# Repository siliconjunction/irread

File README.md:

# Analyse and Send IR Remote Codes

## Overview

The program is used to analyse IR remote control codes and extract the parameters for the coding scheme. It can also send IR codes for testing. The hardware required is based on the ESP8266. The software is written in C on Mongoose OS.

<br/>
<center></center>
<br/>

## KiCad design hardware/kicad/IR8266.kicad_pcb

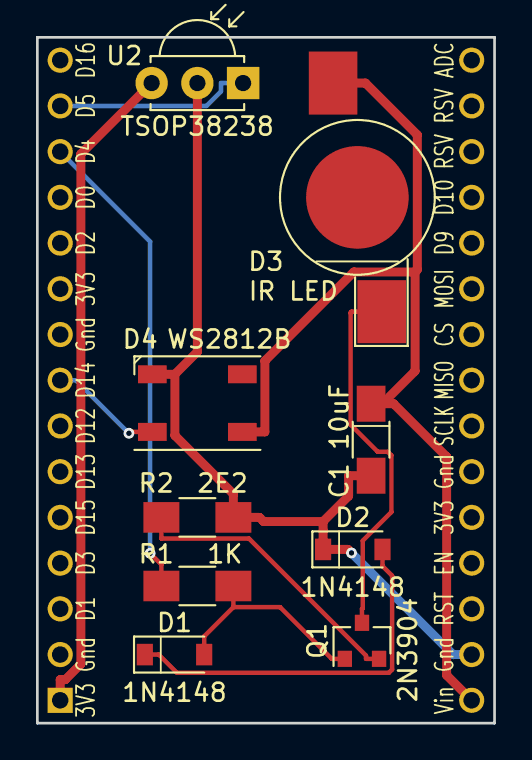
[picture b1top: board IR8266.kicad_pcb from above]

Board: 2 copper layers, 25.4 x 38.1 mm, 10 parts (1 on the bottom side), 10 nets.

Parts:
C1: 10uF; C_1206_HandSoldering
D1, D2: 1N4148; D_SOD-123
D3: IR LED; LED_1W_3W_R8
D4: WS2812B; LED_WS2812B-PLCC4
Q1: 2N3904; SOT-23
R1: 1K; R_1206_HandSoldering
R2: 2E2; R_1206_HandSoldering
U1: ESP8266-DEVKIT; ESP8266_DEV_KIT
U2: TSOP38238; IRReceiver_Vishay_MINICAST-3pin

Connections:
+3V3: U1.1, U2.3
+5V: C1.1, D3.2, D4.1, U1.30
GND: C1.2, D2.1, D4.3, R2.2, U1.29, U2.2
unnamed: D1.1, D2.2
unnamed: D1.2, Q1.1, R1.2
unnamed: D3.1, Q1.3
unnamed: D4.4, U1.8
unnamed: Q1.2, R2.1
unnamed: R1.1, U1.13
unnamed: U1.14, U2.1

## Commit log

2018-04-24 Rel 1.0
    First release
2018-04-24 Replaced standard template with a real readme file
2018-04-24 Added hardware resources
    Added Kicad schematic and PCB design. Added gerber files.
2018-04-24 Added hardware image
